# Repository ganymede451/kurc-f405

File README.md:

# KURC F405 Flight Controller

A 40×40 mm, 4-layer STM32F405 flight controller for Betaflight,
designed in KiCad.
Pin mapping follows the SpeedyBee F405 V3 (`SPEEDYBEEF405V3` target).

## Specs
| | |
|---|---|
| MCU | STM32F405RGT6 (168 MHz) |
| Gyro | BMI270 (SPI) |
| Input | 2S–6S LiPo |
| Regulators | TPS54360 buck → 5 V, AP2112K LDO → 3.3 V |
| USB | USB-C |
| Storage | microSD (blackbox) |
| Size | 40×40 mm, 30.5 mm mounting holes, 4-layer |
| ESC | External 4-in-1 via 8-pin JST-SH |

## Layer stack

1. **F.Cu**: components and signals
2. **In1**: GND plane
3. **In2**: +3V3 plane
4. **B.Cu**: signals, wire pads, microSD socket

## Repo layout
| Folder | Contents |
|---|---|
| `hardware/` | KiCad project (open `kurc_f405.kicad_pro`) |
| `fabrication/` | Gerber zip and BOM for ordering |
| `docs/` | Schematic PDF and images |
| `firmware/` | Betaflight setup notes |

## Firmware
Flash the Betaflight `SPEEDYBEEF405V3` target, then apply any
remaps from `firmware/betaflight_resources.txt` in the CLI.

## Status
- [x] Schematic
- [x] Placement and routing (DRC clean, 0 unconnected)
- [ ] Fabrication (rev 1)
- [ ] Bring-up and flight test

## Known issues / rev 2 ideas
- Buck converter layout is spread out (long switch node); tighten in rev 2
- VCAP caps (C19/C20) could sit closer to the MCU
- Add 100 nF decoupling right at MCU pin 48

## Tools
KiCad 10 · Arch Linux

## License
Hardware: CERN-OHL-S-2.0

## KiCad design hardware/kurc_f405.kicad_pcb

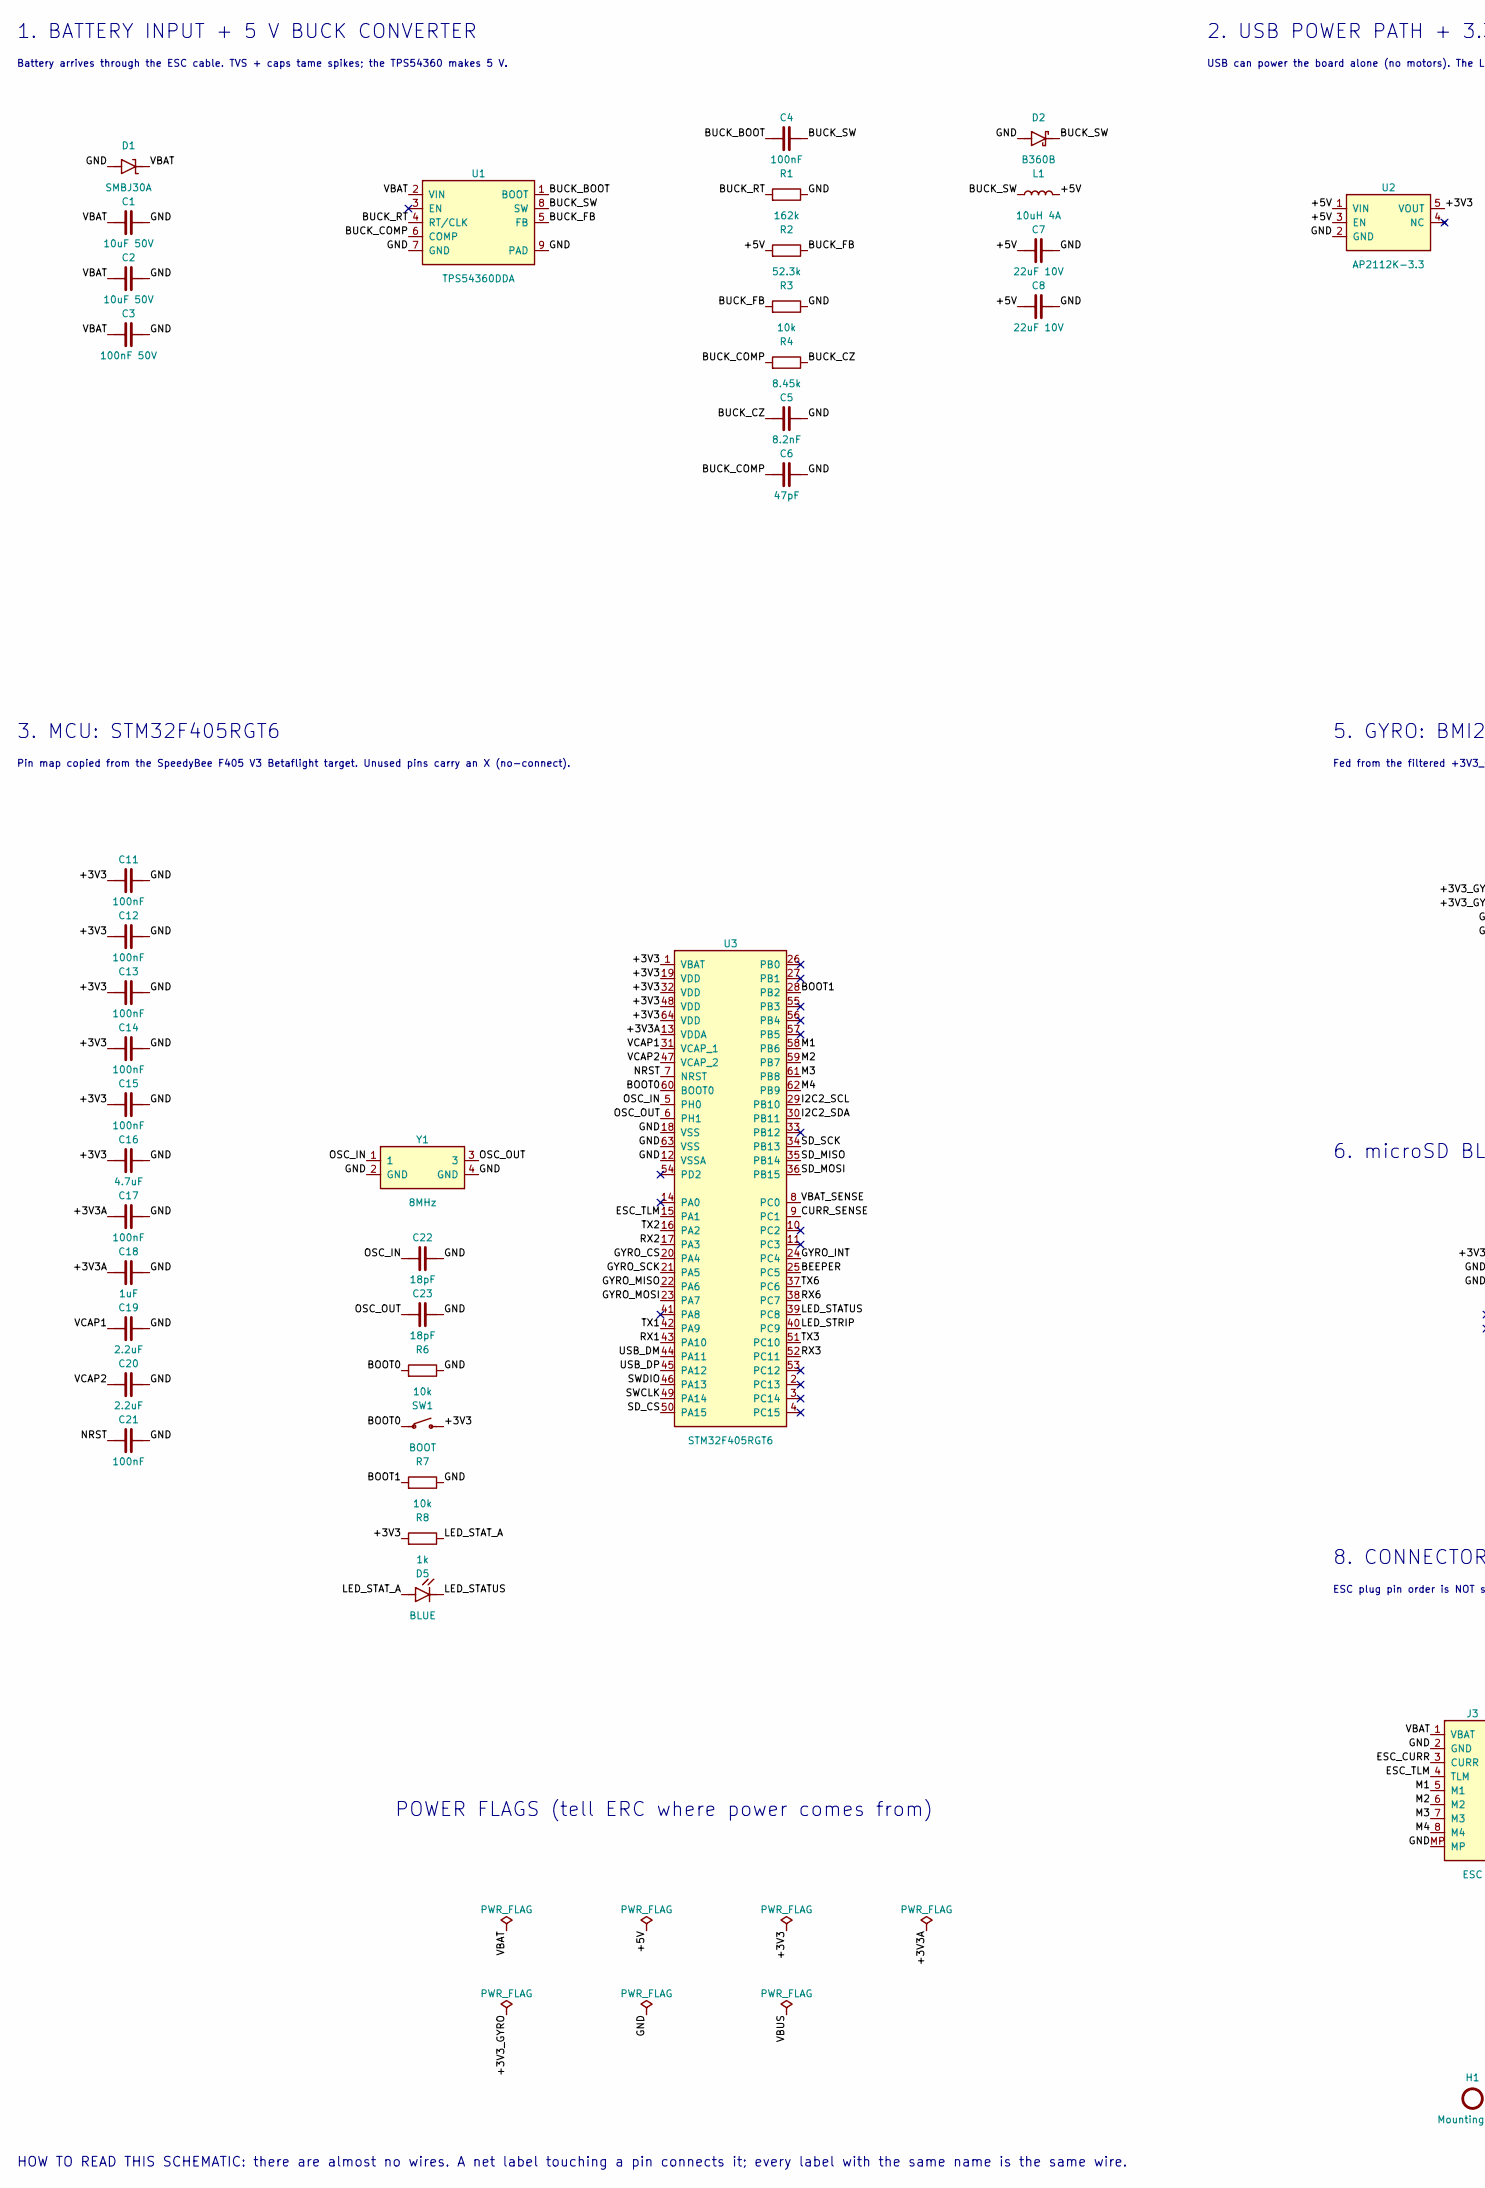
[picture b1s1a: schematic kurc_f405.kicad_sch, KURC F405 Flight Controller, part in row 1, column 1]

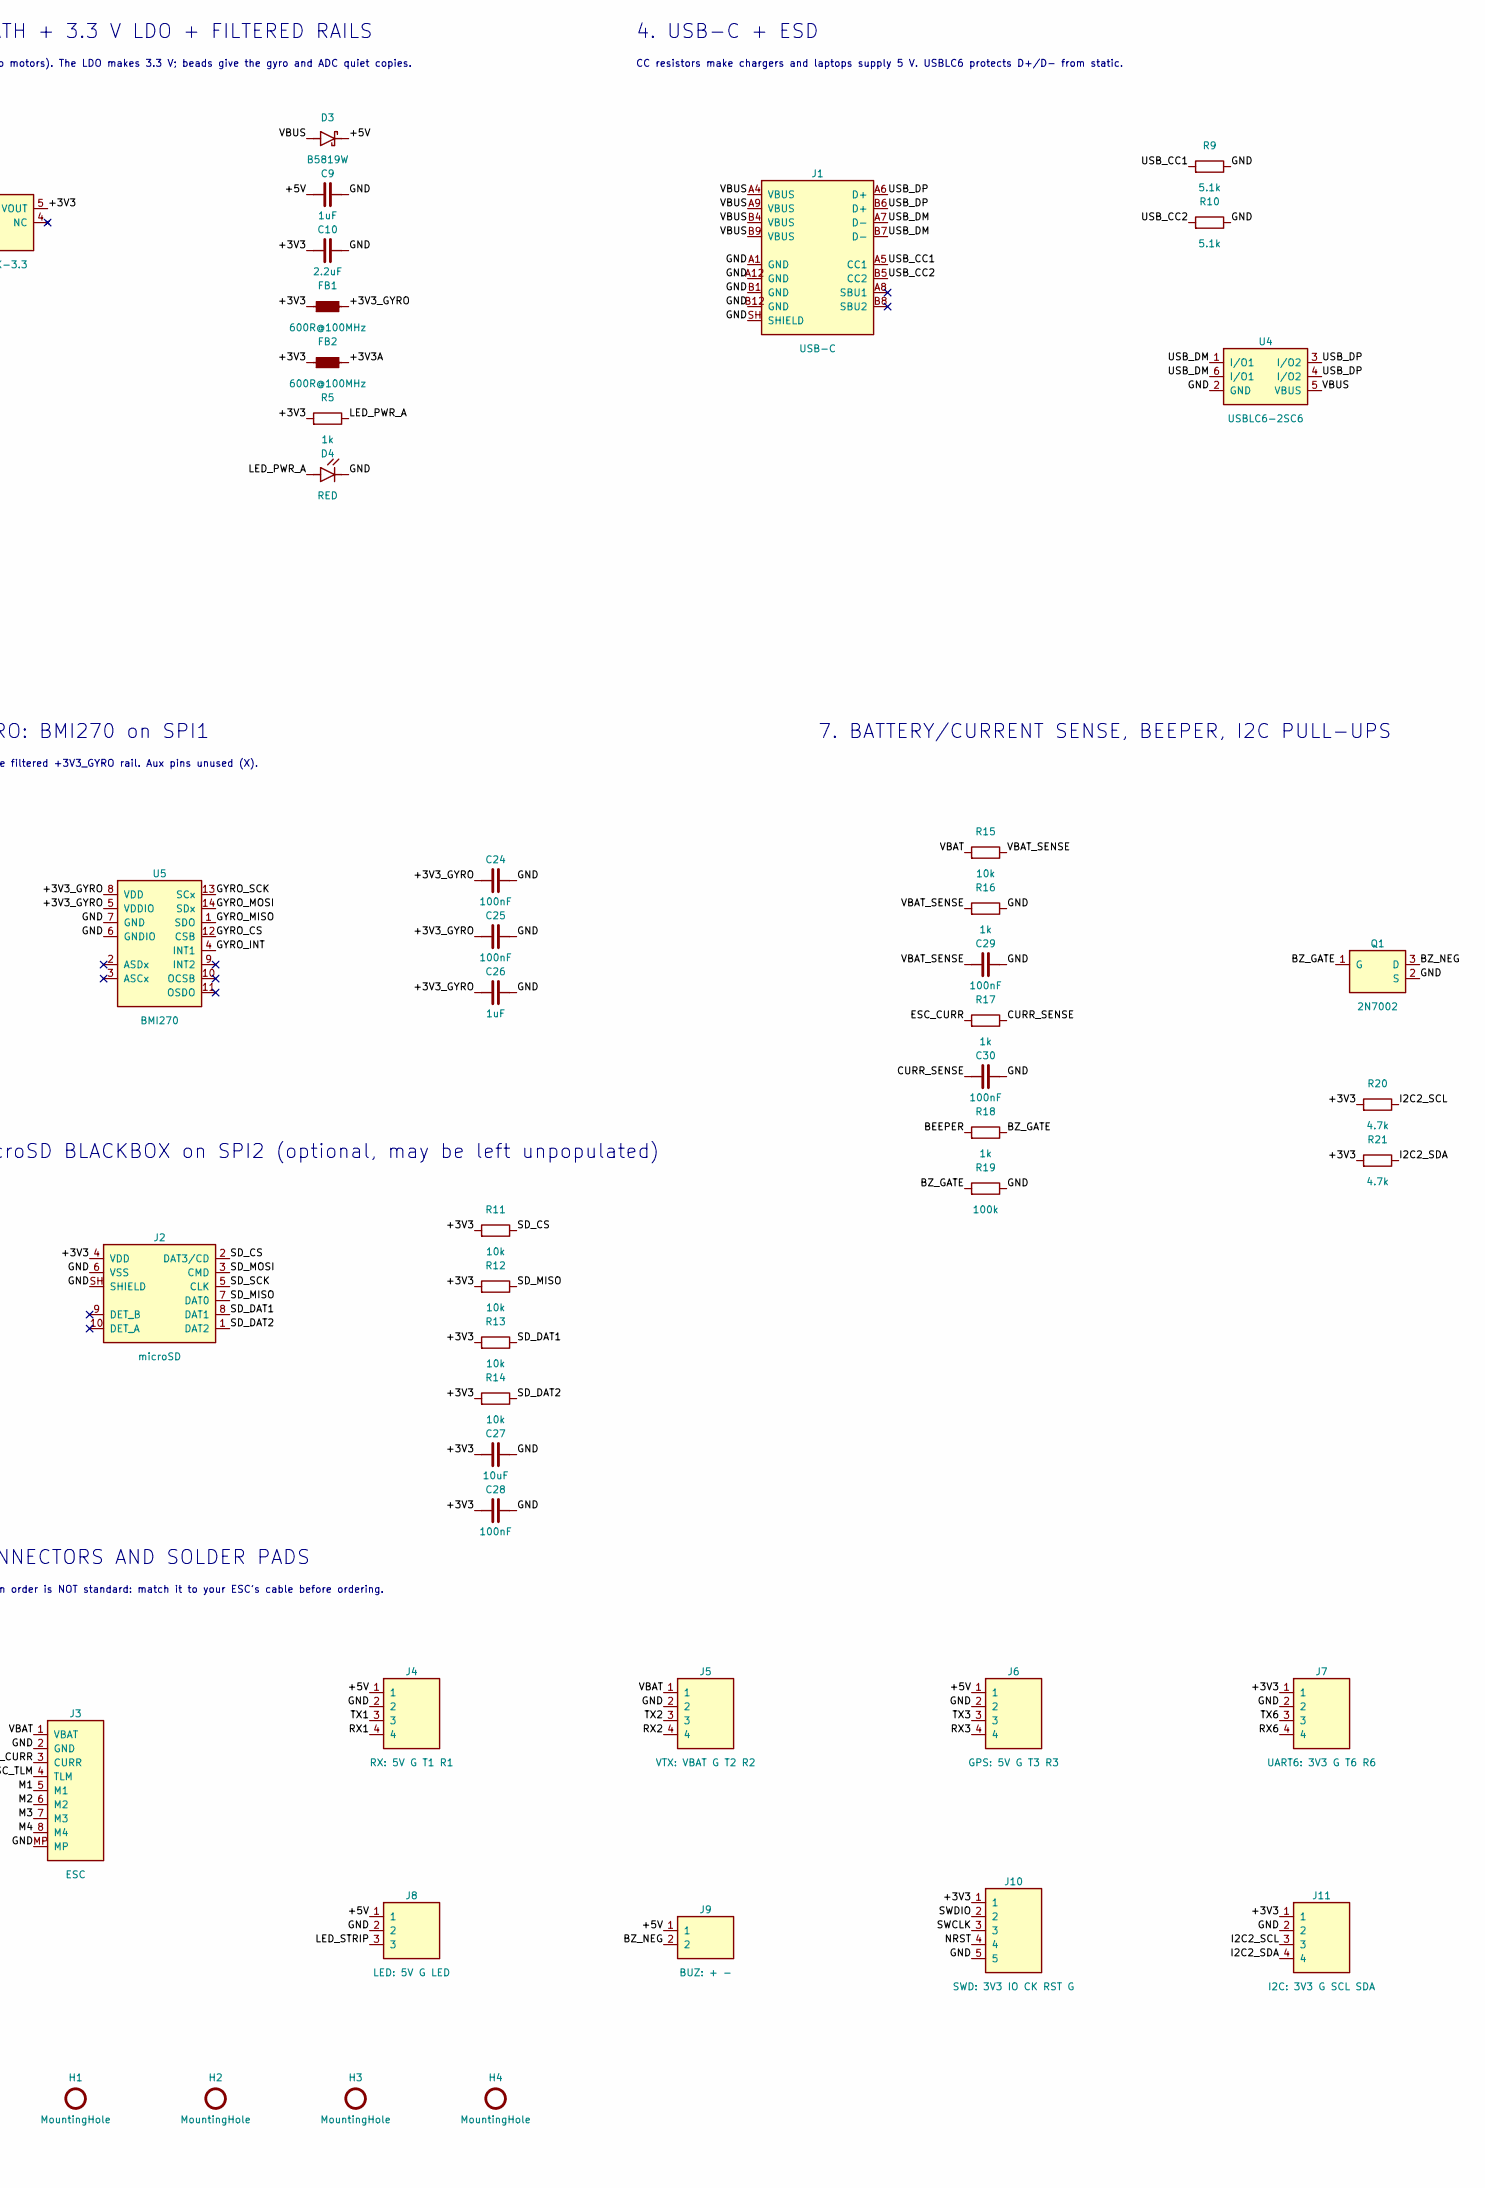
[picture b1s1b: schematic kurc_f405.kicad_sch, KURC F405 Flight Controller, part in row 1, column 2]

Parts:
C1, C2: 10uF 50V; C_1206_3216Metric; MPN 1206 10uF 50V X7R/X5R
C3: 100nF 50V; C_0603_1608Metric; MPN 0603 100nF 50V X7R/X5R
C4: 100nF; C_0603_1608Metric; MPN 0603 100nF X7R/X5R
C5: 8.2nF; C_0402_1005Metric; MPN 0402 8.2nF X7R/X5R
C6: 47pF; C_0402_1005Metric; MPN 0402 47pF X7R/X5R
C7, C8: 22uF 10V; C_0805_2012Metric; MPN 0805 22uF 10V X7R/X5R
C9, C18, C26: 1uF; C_0603_1608Metric; MPN 0603 1uF X7R/X5R
C10, C19, C20: 2.2uF; C_0603_1608Metric; MPN 0603 2.2uF X7R/X5R
C11, C12, C13, C14, C15, C17, C21, C24, C25, C28, C29, C30: 100nF; C_0402_1005Metric; MPN 0402 100nF X7R/X5R
C16: 4.7uF; C_0603_1608Metric; MPN 0603 4.7uF X7R/X5R
C22, C23: 18pF; C_0402_1005Metric; MPN 0402 18pF X7R/X5R
C27: 10uF; C_0805_2012Metric; MPN 0805 10uF X7R/X5R
D1: SMBJ30A; D_SMB; MPN SMBJ30A
D2: B360B; D_SMB; MPN B360B-13-F
D3: B5819W; D_SOD-123; MPN B5819W
D4: RED; LED_0603_1608Metric; MPN 0603 red LED
D5: BLUE; LED_0603_1608Metric; MPN 0603 blue LED
FB1, FB2: 600R@100MHz; L_0603_1608Metric; MPN BLM18PG601SN1D
H1, H2, H3, H4: MountingHole; MountingHole_4.0mm_Grommet
J1: USB-C; USB_C_Receptacle_HRO_TYPE-C-31-M-12; MPN HRO TYPE-C-31-M-12
J2: microSD; microSD_HC_Hirose_DM3AT-SF-PEJM5; MPN Hirose DM3AT-SF-PEJM5
J3: ESC; JST_SH_SM08B-SRSS-TB_1x08-1MP_P1.00mm_Horizontal; MPN JST SM08B-SRSS-TB
J4: RX: 5V G T1 R1; SolderPads_1x04_P2.54mm
J5: VTX: VBAT G T2 R2; SolderPads_1x04_P2.54mm
J6: GPS: 5V G T3 R3; SolderPads_1x04_P2.54mm
J7: UART6: 3V3 G T6 R6; SolderPads_1x04_P2.54mm
J8: LED: 5V G LED; SolderPads_1x03_P2.54mm
J9: BUZ: + -; SolderPads_1x02_P2.54mm
J10: SWD: 3V3 IO CK RST G; SolderPads_1x05_P2.54mm
J11: I2C: 3V3 G SCL SDA; SolderPads_1x04_P2.54mm
L1: 10uH 4A; L_Bourns_SRN8040TA; MPN SRN8040TA-100M
Q1: 2N7002; SOT-23; MPN 2N7002
R1: 162k; R_0603_1608Metric; MPN 0603 162k 1%
R2: 52.3k; R_0603_1608Metric; MPN 0603 52.3k 1%
R3, R6, R7, R11, R12, R13, R14, R15: 10k; R_0603_1608Metric; MPN 0603 10k 1%
R4: 8.45k; R_0603_1608Metric; MPN 0603 8.45k 1%
R5, R8, R16, R17, R18: 1k; R_0603_1608Metric; MPN 0603 1k 1%
R9, R10: 5.1k; R_0603_1608Metric; MPN 0603 5.1k 1%
R19: 100k; R_0603_1608Metric; MPN 0603 100k 1%
R20, R21: 4.7k; R_0603_1608Metric; MPN 0603 4.7k 1%
SW1: BOOT; SW_SPST_PTS810; MPN C&K PTS810 SJM 250 SMTR LFS
U1: TPS54360DDA; TI_SO-PowerPAD-8_ThermalVias; MPN TPS54360DDAR
U2: AP2112K-3.3; SOT-23-5; MPN AP2112K-3.3TRG1
U3: STM32F405RGT6; LQFP-64_10x10mm_P0.5mm; MPN STM32F405RGT6
U4: USBLC6-2SC6; SOT-23-6; MPN USBLC6-2SC6
U5: BMI270; Bosch_LGA-14_3x2.5mm_P0.5mm; MPN BMI270
Y1: 8MHz; Crystal_SMD_3225-4Pin_3.2x2.5mm; MPN 8 MHz 3225 crystal, CL 12 pF

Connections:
/+3V3: C10.1, C11.1, C12.1, C13.1, C14.1, C15.1, C16.1, C27.1, C28.1, FB1.1, FB2.1, J2.4 (VDD), J7.1, J10.1, J11.1, R5.1, R8.1, R11.1, R12.1, R13.1, R14.1, R20.1, R21.1, SW1.2, U2.5 (VOUT), U3.1 (VBAT), U3.19 (VDD), U3.32 (VDD), U3.48 (VDD), U3.64 (VDD)
/+3V3A: C17.1, C18.1, FB2.2, U3.13 (VDDA)
/+3V3_GYRO: C24.1, C25.1, C26.1, FB1.2, U5.5 (VDDIO), U5.8 (VDD)
/+5V: C7.1, C8.1, C9.1, D3.1 (K), J4.1, J6.1, J8.1, J9.1, L1.2, R2.1, U2.1 (VIN), U2.3 (EN)
/BEEPER: R18.1, U3.25 (PC5)
/BOOT0: R6.1, SW1.1, U3.60 (BOOT0)
/BOOT1: R7.1, U3.28 (PB2)
/BUCK_BOOT: C4.1, U1.1 (BOOT)
/BUCK_COMP: C6.1, R4.1, U1.6 (COMP)
/BUCK_CZ: C5.1, R4.2
/BUCK_FB: R2.2, R3.1, U1.5 (FB)
/BUCK_RT: R1.1, U1.4 (RT/CLK)
/BUCK_SW: C4.2, D2.1 (K), L1.1, U1.8 (SW)
/BZ_GATE: Q1.1 (G), R18.2, R19.1
/BZ_NEG: J9.2, Q1.3 (D)
/CURR_SENSE: C30.1, R17.2, U3.9 (PC1)
/ESC_CURR: J3.3 (CURR), R17.1
/ESC_TLM: J3.4 (TLM), U3.15 (PA1)
/GND: C1.2, C2.2, C3.2, C5.2, C6.2, C7.2, C8.2, C9.2, C10.2, C11.2, C12.2, C13.2, C14.2, C15.2, C16.2, C17.2, C18.2, C19.2, C20.2, C21.2, C22.2, C23.2, C24.2, C25.2, C26.2, C27.2, C28.2, C29.2, C30.2, D1.2 (A), D2.2 (A), D4.1 (K), J1.A1 (GND), J1.A12 (GND), J1.B1 (GND), J1.B12 (GND), J1.SH (SHIELD), J2.6 (VSS), J2.SH (SHIELD), J3.2 (GND), J3.MP, J4.2, J5.2, J6.2, J7.2, J8.2, J10.5, J11.2, Q1.2 (S), R1.2, R3.2, R6.2, R7.2, R9.2, R10.2, R16.2, R19.2, U1.7 (GND), U1.9 (PAD), U2.2 (GND), U3.12 (VSSA), U3.18 (VSS), U3.63 (VSS), U4.2 (GND), U5.6 (GNDIO), U5.7 (GND), Y1.2 (GND), Y1.4 (GND)
/GYRO_CS: U3.20 (PA4), U5.12 (CSB)
/GYRO_INT: U3.24 (PC4), U5.4 (INT1)
/GYRO_MISO: U3.22 (PA6), U5.1 (SDO)
/GYRO_MOSI: U3.23 (PA7), U5.14 (SDx)
/GYRO_SCK: U3.21 (PA5), U5.13 (SCx)
/I2C2_SCL: J11.3, R20.2, U3.29 (PB10)
/I2C2_SDA: J11.4, R21.2, U3.30 (PB11)
/LED_PWR_A: D4.2 (A), R5.2
/LED_STATUS: D5.1 (K), U3.39 (PC8)
/LED_STAT_A: D5.2 (A), R8.2
/LED_STRIP: J8.3, U3.40 (PC9)
/M1: J3.5 (M1), U3.58 (PB6)
/M2: J3.6 (M2), U3.59 (PB7)
/M3: J3.7 (M3), U3.61 (PB8)
/M4: J3.8 (M4), U3.62 (PB9)
/NRST: C21.1, J10.4, U3.7 (NRST)
/OSC_IN: C22.1, U3.5 (PH0), Y1.1
/OSC_OUT: C23.1, U3.6 (PH1), Y1.3
/RX1: J4.4, U3.43 (PA10)
/RX2: J5.4, U3.17 (PA3)
/RX3: J6.4, U3.52 (PC11)
/RX6: J7.4, U3.38 (PC7)
/SD_CS: J2.2 (DAT3/CD), R11.2, U3.50 (PA15)
/SD_DAT1: J2.8 (DAT1), R13.2
/SD_DAT2: J2.1 (DAT2), R14.2
/SD_MISO: J2.7 (DAT0), R12.2, U3.35 (PB14)
/SD_MOSI: J2.3 (CMD), U3.36 (PB15)
/SD_SCK: J2.5 (CLK), U3.34 (PB13)
/SWCLK: J10.3, U3.49 (PA14)
/SWDIO: J10.2, U3.46 (PA13)
/TX1: J4.3, U3.42 (PA9)
/TX2: J5.3, U3.16 (PA2)
/TX3: J6.3, U3.51 (PC10)
/TX6: J7.3, U3.37 (PC6)
/USB_CC1: J1.A5 (CC1), R9.1
/USB_CC2: J1.B5 (CC2), R10.1
/USB_DM: J1.A7 (D-), J1.B7 (D-), U3.44 (PA11), U4.1 (I/O1), U4.6 (I/O1)
/USB_DP: J1.A6 (D+), J1.B6 (D+), U3.45 (PA12), U4.3 (I/O2), U4.4 (I/O2)
/VBAT: C1.1, C2.1, C3.1, D1.1 (K), J3.1 (VBAT), J5.1, R15.1, U1.2 (VIN)
/VBAT_SENSE: C29.1, R15.2, R16.1, U3.8 (PC0)
/VBUS: D3.2 (A), J1.A4 (VBUS), J1.A9 (VBUS), J1.B4 (VBUS), J1.B9 (VBUS), U4.5 (VBUS)
/VCAP1: C19.1, U3.31 (VCAP_1)
/VCAP2: C20.1, U3.47 (VCAP_2)

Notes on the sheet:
HOW TO READ THIS SCHEMATIC: there are almost no wires. A net label touching a pin connects it; every label with the same name is the same wire.
5. GYRO: BMI270 on SPI1
6. microSD BLACKBOX on SPI2 (optional, may be left unpopulated)
Battery arrives through the ESC cable. TVS + caps tame spikes; the TPS54360 makes 5 V.
Pin map copied from the SpeedyBee F405 V3 Betaflight target. Unused pins carry an X (no-connect).
7. BATTERY/CURRENT SENSE, BEEPER, I2C PULL-UPS
1. BATTERY INPUT + 5 V BUCK CONVERTER
8. CONNECTORS AND SOLDER PADS
CC resistors make chargers and laptops supply 5 V. USBLC6 protects D+/D- from static.
POWER FLAGS (tell ERC where power comes from)
3. MCU: STM32F405RGT6
4. USB-C + ESD
2. USB POWER PATH + 3.3 V LDO + FILTERED RAILS
USB can power the board alone (no motors). The LDO makes 3.3 V; beads give the gyro and ADC quiet copies.
Fed from the filtered +3V3_GYRO rail. Aux pins unused (X).
ESC plug pin order is NOT standard: match it to your ESC's cable before ordering.

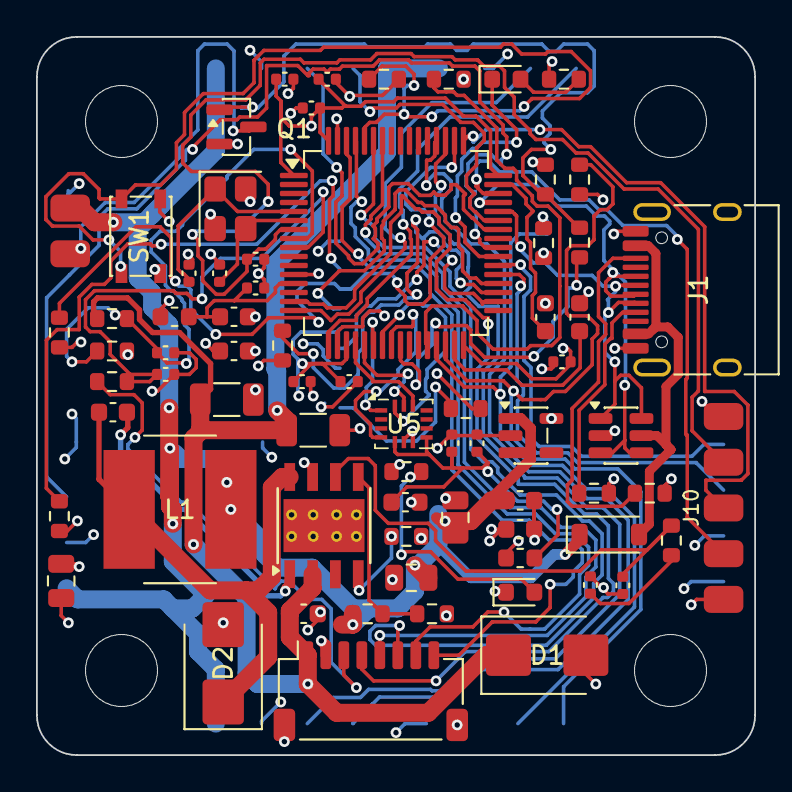
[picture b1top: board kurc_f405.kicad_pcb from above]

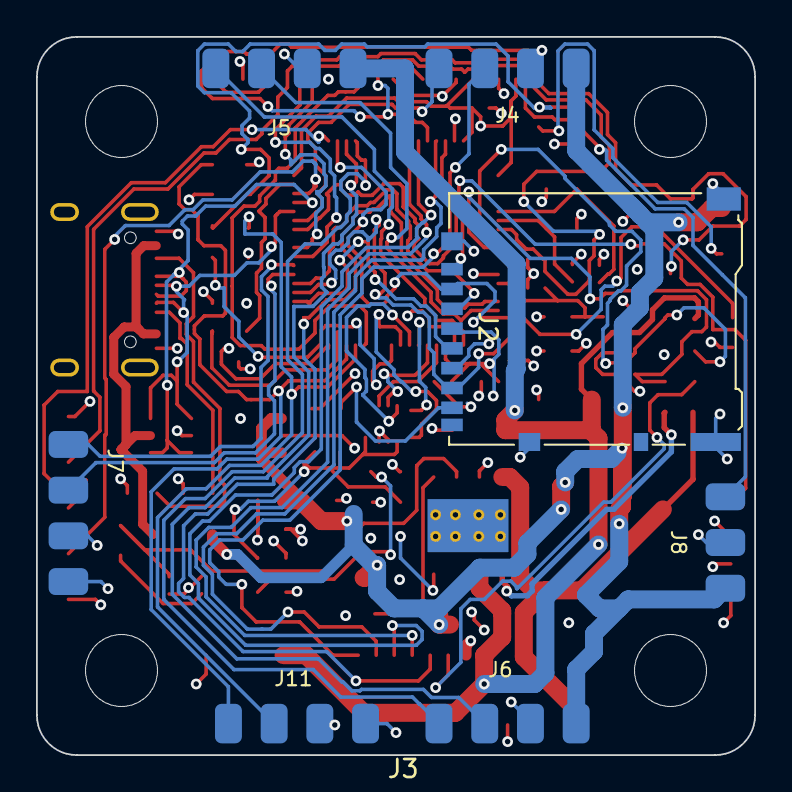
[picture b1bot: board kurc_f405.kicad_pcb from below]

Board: 4 copper layers, 39.9 x 39.9 mm, 82 parts (7 on the bottom side), 62 nets.

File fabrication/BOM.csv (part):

Reference,Value,Footprint,MPN,LCSC (fill in),Block,Why it is there
D1,SMBJ30A,Diode_SMD:D_SMB,SMBJ30A,,1 Power in + 5V buck,TVS: clamps ESC voltage spikes on the battery line
C1,10uF 50V,Capacitor_SMD:C_1206_3216Metric,1206 10uF 50V X7R/X5R,,1 Power in + 5V buck,Buck input cap (bulk)
C2,10uF 50V,Capacitor_SMD:C_1206_3216Metric,1206 10uF 50V X7R/X5R,,1 Power in + 5V buck,Buck input cap (bulk)
C3,100nF 50V,Capacitor_SMD:C_0603_1608Metric,0603 100nF 50V X7R/X5R,,1 Power in + 5V buck,"Buck input cap (high-frequency), right at VIN"
U1,TPS54360DDA,Package_SO:TI_SO-PowerPAD-8_ThermalVias,TPS54360DDAR,,1 Power in + 5V buck,Buck converter: battery (7-25 V) to 5 V
C4,100nF,Capacitor_SMD:C_0603_1608Metric,0603 100nF X7R/X5R,,1 Power in + 5V buck,Bootstrap cap: powers the buck's internal high-side switch
R1,162k,Resistor_SMD:R_0603_1608Metric,0603 162k 1%,,1 Power in + 5V buck,Sets switching frequency to about 600 kHz
R2,52.3k,Resistor_SMD:R_0603_1608Metric,0603 52.3k 1%,,1 Power in + 5V buck,Feedback divider top: sets output to 5.0 V
R3,10k,Resistor_SMD:R_0603_1608Metric,0603 10k 1%,,1 Power in + 5V buck,Feedback divider bottom
R4,8.45k,Resistor_SMD:R_0603_1608Metric,0603 8.45k 1%,,1 Power in + 5V buck,Compensation resistor: keeps the 5 V loop stable (confirm in WEBENCH)
C5,8.2nF,Capacitor_SMD:C_0402_1005Metric,0402 8.2nF X7R/X5R,,1 Power in + 5V buck,Compensation cap (confirm in WEBENCH)
C6,47pF,Capacitor_SMD:C_0402_1005Metric,0402 47pF X7R/X5R,,1 Power in + 5V buck,Compensation high-frequency pole cap (confirm in WEBENCH)
D2,B360B,Diode_SMD:D_SMB,B360B-13-F,,1 Power in + 5V buck,Catch diode: carries inductor current while the switch is off
L1,10uH 4A,Inductor_SMD:L_Bourns_SRN8040TA,SRN8040TA-100M,,1 Power in + 5V buck,Buck inductor: stores and smooths energy
C7,22uF 10V,Capacitor_SMD:C_0805_2012Metric,0805 22uF 10V X7R/X5R,,1 Power in + 5V buck,5 V output cap
C8,22uF 10V,Capacitor_SMD:C_0805_2012Metric,0805 22uF 10V X7R/X5R,,1 Power in + 5V buck,5 V output cap
D3,B5819W,Diode_SMD:D_SOD-123,B5819W,,2 USB power + 3.3V,"Lets USB power the board, blocks battery 5 V from flowing back into the PC"
U2,AP2112K-3.3,Package_TO_SOT_SMD:SOT-23-5,AP2112K-3.3TRG1,,2 USB power + 3.3V,"LDO: clean 3.3 V for MCU, gyro, SD"
C9,1uF,Capacitor_SMD:C_0603_1608Metric,0603 1uF X7R/X5R,,2 USB power + 3.3V,LDO input cap
C10,2.2uF,Capacitor_SMD:C_0603_1608Metric,0603 2.2uF X7R/X5R,,2 USB power + 3.3V,LDO output cap (stability)
FB1,600R@100MHz,Inductor_SMD:L_0603_1608Metric,BLM18PG601SN1D,,2 USB power + 3.3V,Ferrite bead: filters digital noise out of the gyro supply
FB2,600R@100MHz,Inductor_SMD:L_0603_1608Metric,BLM18PG601SN1D,,2 USB power + 3.3V,Ferrite bead: filters noise out of the MCU analog supply (ADC)
R5,1k,Resistor_SMD:R_0603_1608Metric,0603 1k 1%,,2 USB power + 3.3V,Current limit for power LED (about 1 mA)
D4,RED,LED_SMD:LED_0603_1608Metric,0603 red LED,,2 USB power + 3.3V,Power LED: on when 3.3 V is present
U3,STM32F405RGT6,Package_QFP:LQFP-64_10x10mm_P0.5mm,STM32F405RGT6,,3 MCU,The MCU: runs Betaflight
C11,100nF,Capacitor_SMD:C_0402_1005Metric,0402 100nF X7R/X5R,,3 MCU,Decoupling at MCU VDD pin 19
C12,100nF,Capacitor_SMD:C_0402_1005Metric,0402 100nF X7R/X5R,,3 MCU,Decoupling at MCU VDD pin 32
C13,100nF,Capacitor_SMD:C_0402_1005Metric,0402 100nF X7R/X5R,,3 MCU,Decoupling at MCU VDD pin 48
C14,100nF,Capacitor_SMD:C_0402_1005Metric,0402 100nF X7R/X5R,,3 MCU,Decoupling at MCU VDD pin 64
C15,100nF,Capacitor_SMD:C_0402_1005Metric,0402 100nF X7R/X5R,,3 MCU,Decoupling at MCU VBAT pin 1
C16,4.7uF,Capacitor_SMD:C_0603_1608Metric,0603 4.7uF X7R/X5R,,3 MCU,Bulk cap for the MCU 3.3 V rail
C17,100nF,Capacitor_SMD:C_0402_1005Metric,0402 100nF X7R/X5R,,3 MCU,Decoupling at VDDA (analog supply)
C18,1uF,Capacitor_SMD:C_0603_1608Metric,0603 1uF X7R/X5R,,3 MCU,Bulk cap at VDDA
C19,2.2uF,Capacitor_SMD:C_0603_1608Metric,0603 2.2uF X7R/X5R,,3 MCU,Required by MCU internal 1.2 V core regulator (VCAP_1)
C20,2.2uF,Capacitor_SMD:C_0603_1608Metric,0603 2.2uF X7R/X5R,,3 MCU,Required by MCU internal 1.2 V core regulator (VCAP_2)
C21,100nF,Capacitor_SMD:C_0402_1005Metric,0402 100nF X7R/X5R,,3 MCU,Reset filter: clean reset at power-up
Y1,8MHz,Crystal:Crystal_SMD_3225-4Pin_3.2x2.5mm,"8 MHz 3225 crystal, CL 12 pF",,3 MCU,8 MHz crystal: precise clock (needed for USB and Betaflight timing)
C22,18pF,Capacitor_SMD:C_0402_1005Metric,0402 18pF X7R/X5R,,3 MCU,Crystal load cap
C23,18pF,Capacitor_SMD:C_0402_1005Metric,0402 18pF X7R/X5R,,3 MCU,Crystal load cap
R6,10k,Resistor_SMD:R_0603_1608Metric,0603 10k 1%,,3 MCU,BOOT0 pull-down: normal start-up runs Betaflight
SW1,BOOT,Button_Switch_SMD:SW_SPST_PTS810,C&K PTS810 SJM 250 SMTR LFS,,3 MCU,BOOT button: hold while plugging USB to enter flashing (DFU) mode
R7,10k,Resistor_SMD:R_0603_1608Metric,0603 10k 1%,,3 MCU,BOOT1 (PB2) pull-down
R8,1k,Resistor_SMD:R_0603_1608Metric,0603 1k 1%,,3 MCU,Current limit for status LED
D5,BLUE,LED_SMD:LED_0603_1608Metric,0603 blue LED,,3 MCU,"Status LED, driven by Betaflight (PC8 pulls low = on)"
J1,USB-C,Connector_USB:USB_C_Receptacle_HRO_TYPE-C-31-M-12,HRO TYPE-C-31-M-12,,4 USB-C,"USB-C socket: configure, flash, power on the bench"
R9,5.1k,Resistor_SMD:R_0603_1608Metric,0603 5.1k 1%,,4 USB-C,CC1 pull-down: tells USB-C sources to supply 5 V
R10,5.1k,Resistor_SMD:R_0603_1608Metric,0603 5.1k 1%,,4 USB-C,CC2 pull-down (for the other plug orientation)
U4,USBLC6-2SC6,Package_TO_SOT_SMD:SOT-23-6,USBLC6-2SC6,,4 USB-C,ESD protection for USB data lines
U5,BMI270,Package_LGA:Bosch_LGA-14_3x2.5mm_P0.5mm,BMI270,,5 Gyro,Gyro + accelerometer on SPI1
C24,100nF,Capacitor_SMD:C_0402_1005Metric,0402 100nF X7R/X5R,,5 Gyro,Decoupling at gyro VDD
C25,100nF,Capacitor_SMD:C_0402_1005Metric,0402 100nF X7R/X5R,,5 Gyro,Decoupling at gyro VDDIO
C26,1uF,Capacitor_SMD:C_0603_1608Metric,0603 1uF X7R/X5R,,5 Gyro,Bulk cap for gyro supply
J2,microSD,Connector_Card:microSD_HC_Hirose_DM3AT-SF-PEJM5,Hirose DM3AT-SF-PEJM5,,6 microSD (optional),Blackbox log card socket (SPI2)
R11,10k,Resistor_SMD:R_0603_1608Metric,0603 10k 1%,,6 microSD (optional),Pull-up: card stays deselected while MCU boots
R12,10k,Resistor_SMD:R_0603_1608Metric,0603 10k 1%,,6 microSD (optional),Pull-up on card data out
R13,10k,Resistor_SMD:R_0603_1608Metric,0603 10k 1%,,6 microSD (optional),Pull-up: unused card pin held high
R14,10k,Resistor_SMD:R_0603_1608Metric,0603 10k 1%,,6 microSD (optional),Pull-up: unused card pin held high
C27,10uF,Capacitor_SMD:C_0805_2012Metric,0805 10uF X7R/X5R,,6 microSD (optional),Absorbs current spikes when the card writes
C28,100nF,Capacitor_SMD:C_0402_1005Metric,0402 100nF X7R/X5R,,6 microSD (optional),Decoupling at card VDD
R15,10k,Resistor_SMD:R_0603_1608Metric,0603 10k 1%,,"7 Sense, beeper, I2C",Battery divider top (divide by 11)
R16,1k,Resistor_SMD:R_0603_1608Metric,0603 1k 1%,,"7 Sense, beeper, I2C",Battery divider bottom: 25.2 V becomes 2.3 V
C29,100nF,Capacitor_SMD:C_0402_1005Metric,0402 100nF X7R/X5R,,"7 Sense, beeper, I2C",Filters noise on battery reading
R17,1k,Resistor_SMD:R_0603_1608Metric,0603 1k 1%,,"7 Sense, beeper, I2C",Current signal filter resistor
C30,100nF,Capacitor_SMD:C_0402_1005Metric,0402 100nF X7R/X5R,,"7 Sense, beeper, I2C",Current signal filter cap
R18,1k,Resistor_SMD:R_0603_1608Metric,0603 1k 1%,,"7 Sense, beeper, I2C",MOSFET gate resistor
R19,100k,Resistor_SMD:R_0603_1608Metric,0603 100k 1%,,"7 Sense, beeper, I2C",Keeps buzzer silent while MCU boots
Q1,2N7002,Package_TO_SOT_SMD:SOT-23,2N7002,,"7 Sense, beeper, I2C",Switch that turns the buzzer on (MCU pin too weak alone)
R20,4.7k,Resistor_SMD:R_0603_1608Metric,0603 4.7k 1%,,"7 Sense, beeper, I2C",I2C pull-up (for optional baro/compass)
R21,4.7k,Resistor_SMD:R_0603_1608Metric,0603 4.7k 1%,,"7 Sense, beeper, I2C",I2C pull-up (for optional baro/compass)
J3,ESC,Connector_JST:JST_SH_SM08B-SRSS-TB_1x08-1MP_P1.00mm_Horizontal,JST SM08B-SRSS-TB,,8 Connectors + pads,Cable to the 4-in-1 ESC. CHECK pin order against your ESC manual
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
